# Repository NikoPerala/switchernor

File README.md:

# switchernor
Digitaly controlled analog patchbay

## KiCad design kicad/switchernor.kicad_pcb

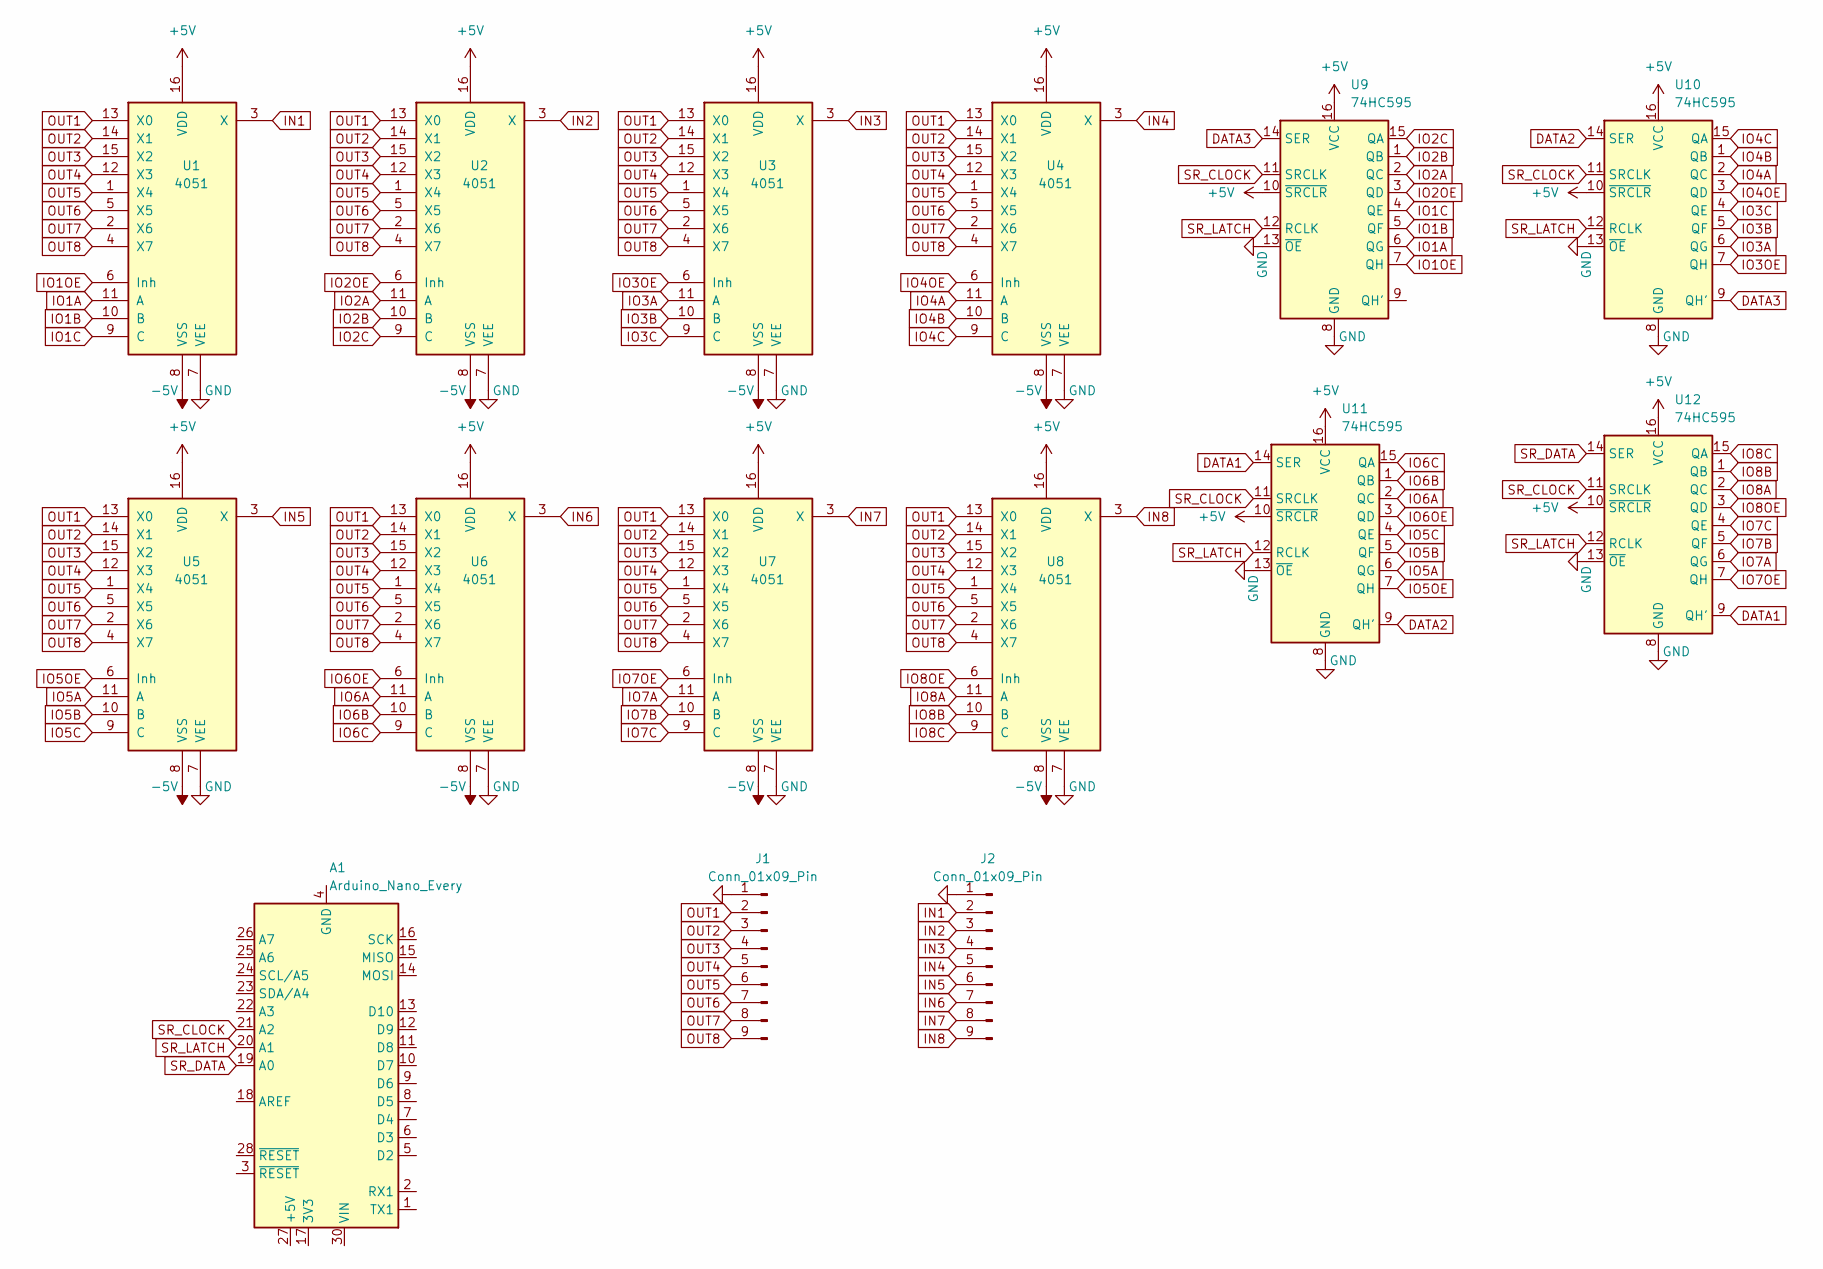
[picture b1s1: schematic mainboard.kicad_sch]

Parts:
A1: Arduino_Nano_Every; Arduino_Nano
J1, J2: Conn_01x09_Pin; PinHeader_2x05_P2.54mm_Vertical
U1, U2, U3, U4, U5, U6, U7, U8: 4051; DIP-16_W7.62mm_Socket_LongPads
U9, U10, U11, U12: 74HC595; DIP-16_W7.62mm_Socket_LongPads

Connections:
+5V: U1.16 (VDD), U2.16 (VDD), U3.16 (VDD), U4.16 (VDD), U5.16 (VDD), U6.16 (VDD), U7.16 (VDD), U8.16 (VDD), U9.10 (~SRCLR), U9.16 (VCC), U10.10 (~SRCLR), U10.16 (VCC), U11.10 (~SRCLR), U11.16 (VCC), U12.10 (~SRCLR), U12.16 (VCC)
-5V: U1.8 (VSS), U2.8 (VSS), U3.8 (VSS), U4.8 (VSS), U5.8 (VSS), U6.8 (VSS), U7.8 (VSS), U8.8 (VSS)
DATA1: U11.14 (SER), U12.9 (QH')
DATA2: U10.14 (SER), U11.9 (QH')
DATA3: U9.14 (SER), U10.9 (QH')
GND: J1.1, J2.1, U1.7 (VEE), U2.7 (VEE), U3.7 (VEE), U4.7 (VEE), U5.7 (VEE), U6.7 (VEE), U7.7 (VEE), U8.7 (VEE), U9.8 (GND), U9.13 (~OE), U10.8 (GND), U10.13 (~OE), U11.8 (GND), U11.13 (~OE), U12.8 (GND), U12.13 (~OE)
IN1: J2.2, U1.3 (X)
IN2: J2.3, U2.3 (X)
IN3: J2.4, U3.3 (X)
IN4: J2.5, U4.3 (X)
IN5: J2.6, U5.3 (X)
IN6: J2.7, U6.3 (X)
IN7: J2.8, U7.3 (X)
IN8: J2.9, U8.3 (X)
IO1A: U1.11 (A), U9.6 (QG)
IO1B: U1.10 (B), U9.5 (QF)
IO1C: U1.9 (C), U9.4 (QE)
IO1OE: U1.6 (Inh), U9.7 (QH)
IO2A: U2.11 (A), U9.2 (QC)
IO2B: U2.10 (B), U9.1 (QB)
IO2C: U2.9 (C), U9.15 (QA)
IO2OE: U2.6 (Inh), U9.3 (QD)
IO3A: U3.11 (A), U10.6 (QG)
IO3B: U3.10 (B), U10.5 (QF)
IO3C: U3.9 (C), U10.4 (QE)
IO3OE: U3.6 (Inh), U10.7 (QH)
IO4A: U4.11 (A), U10.2 (QC)
IO4B: U4.10 (B), U10.1 (QB)
IO4C: U4.9 (C), U10.15 (QA)
IO4OE: U4.6 (Inh), U10.3 (QD)
IO5A: U5.11 (A), U11.6 (QG)
IO5B: U5.10 (B), U11.5 (QF)
IO5C: U5.9 (C), U11.4 (QE)
IO5OE: U5.6 (Inh), U11.7 (QH)
IO6A: U6.11 (A), U11.2 (QC)
IO6B: U6.10 (B), U11.1 (QB)
IO6C: U6.9 (C), U11.15 (QA)
IO6OE: U6.6 (Inh), U11.3 (QD)
IO7A: U7.11 (A), U12.6 (QG)
IO7B: U7.10 (B), U12.5 (QF)
IO7C: U7.9 (C), U12.4 (QE)
IO7OE: U7.6 (Inh), U12.7 (QH)
IO8A: U8.11 (A), U12.2 (QC)
IO8B: U8.10 (B), U12.1 (QB)
IO8C: U8.9 (C), U12.15 (QA)
IO8OE: U8.6 (Inh), U12.3 (QD)
unnamed: A1.4 (GND), A1.29 (GND)
OUT1: J1.2, U1.13 (X0), U2.13 (X0), U3.13 (X0), U4.13 (X0), U5.13 (X0), U6.13 (X0), U7.13 (X0), U8.13 (X0)
OUT2: J1.3, U1.14 (X1), U2.14 (X1), U3.14 (X1), U4.14 (X1), U5.14 (X1), U6.14 (X1), U7.14 (X1), U8.14 (X1)
OUT3: J1.4, U1.15 (X2), U2.15 (X2), U3.15 (X2), U4.15 (X2), U5.15 (X2), U6.15 (X2), U7.15 (X2), U8.15 (X2)
OUT4: J1.5, U1.12 (X3), U2.12 (X3), U3.12 (X3), U4.12 (X3), U5.12 (X3), U6.12 (X3), U7.12 (X3), U8.12 (X3)
OUT5: J1.6, U1.1 (X4), U2.1 (X4), U3.1 (X4), U4.1 (X4), U5.1 (X4), U6.1 (X4), U7.1 (X4), U8.1 (X4)
OUT6: J1.7, U1.5 (X5), U2.5 (X5), U3.5 (X5), U4.5 (X5), U5.5 (X5), U6.5 (X5), U7.5 (X5), U8.5 (X5)
OUT7: J1.8, U1.2 (X6), U2.2 (X6), U3.2 (X6), U4.2 (X6), U5.2 (X6), U6.2 (X6), U7.2 (X6), U8.2 (X6)
OUT8: J1.9, U1.4 (X7), U2.4 (X7), U3.4 (X7), U4.4 (X7), U5.4 (X7), U6.4 (X7), U7.4 (X7), U8.4 (X7)
SR_CLOCK: A1.21 (A2), U9.11 (SRCLK), U10.11 (SRCLK), U11.11 (SRCLK), U12.11 (SRCLK)
SR_DATA: A1.19 (A0), U12.14 (SER)
SR_LATCH: A1.20 (A1), U9.12 (RCLK), U10.12 (RCLK), U11.12 (RCLK), U12.12 (RCLK)

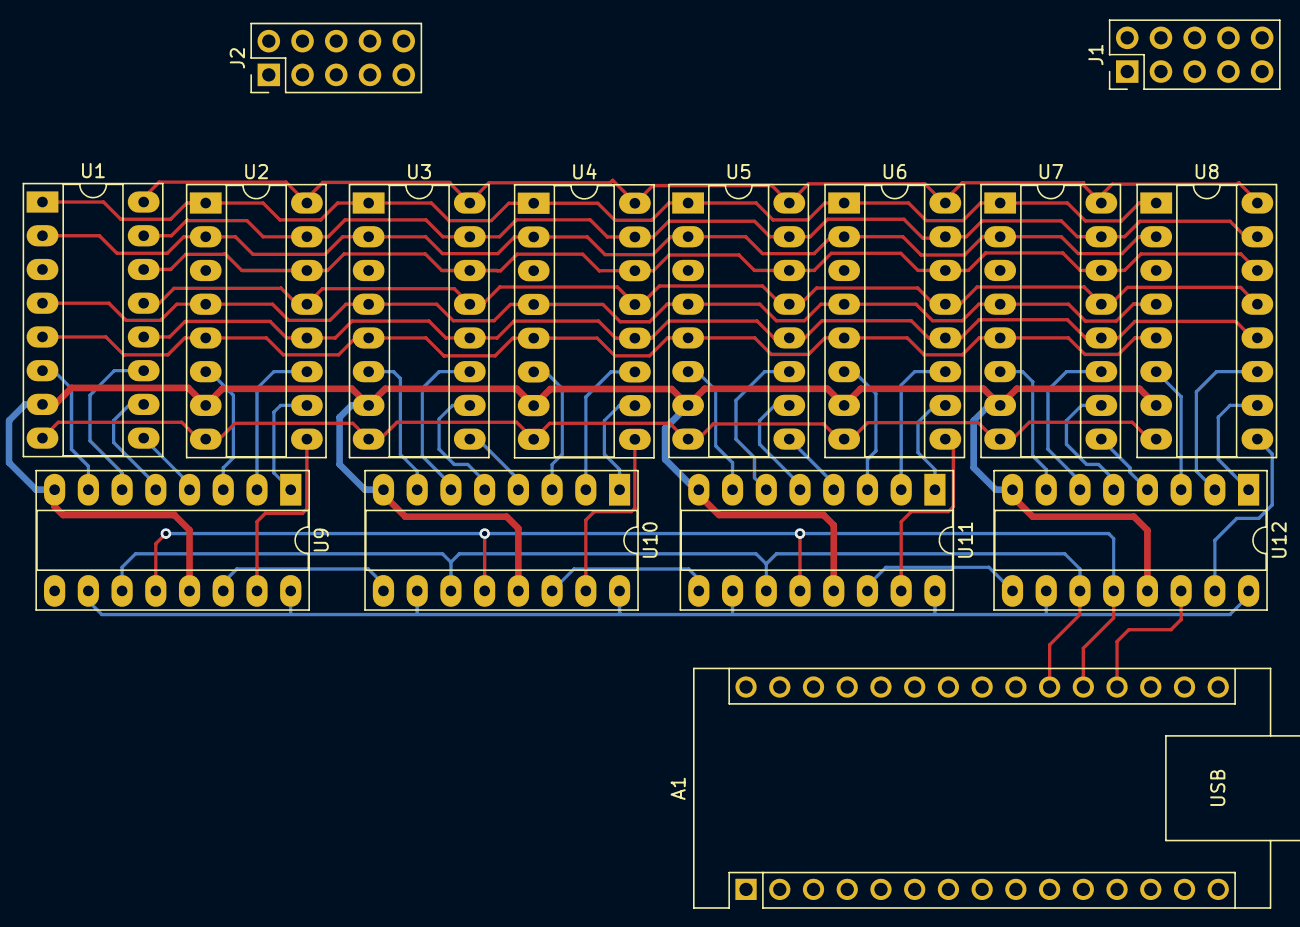
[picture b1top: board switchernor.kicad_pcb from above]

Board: 2 copper layers, 15 parts (0 on the bottom side), 58 nets.

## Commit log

2023-11-15 Added kicad peoject template
2023-11-15 Begining of mainboard schematic
2023-11-15 Added all 5041
2023-11-15 Added data latches
2023-11-16 Scetch of pcb. Uses 74595 for now which is bit slow
2023-11-16 Arduino added
2023-11-19 Created graphical prototype of hardware ui
2023-11-19 added readme to prototype
2023-11-19 updated gitignore
2023-11-19 removed swap file
2023-11-28 Mouse click stuff
